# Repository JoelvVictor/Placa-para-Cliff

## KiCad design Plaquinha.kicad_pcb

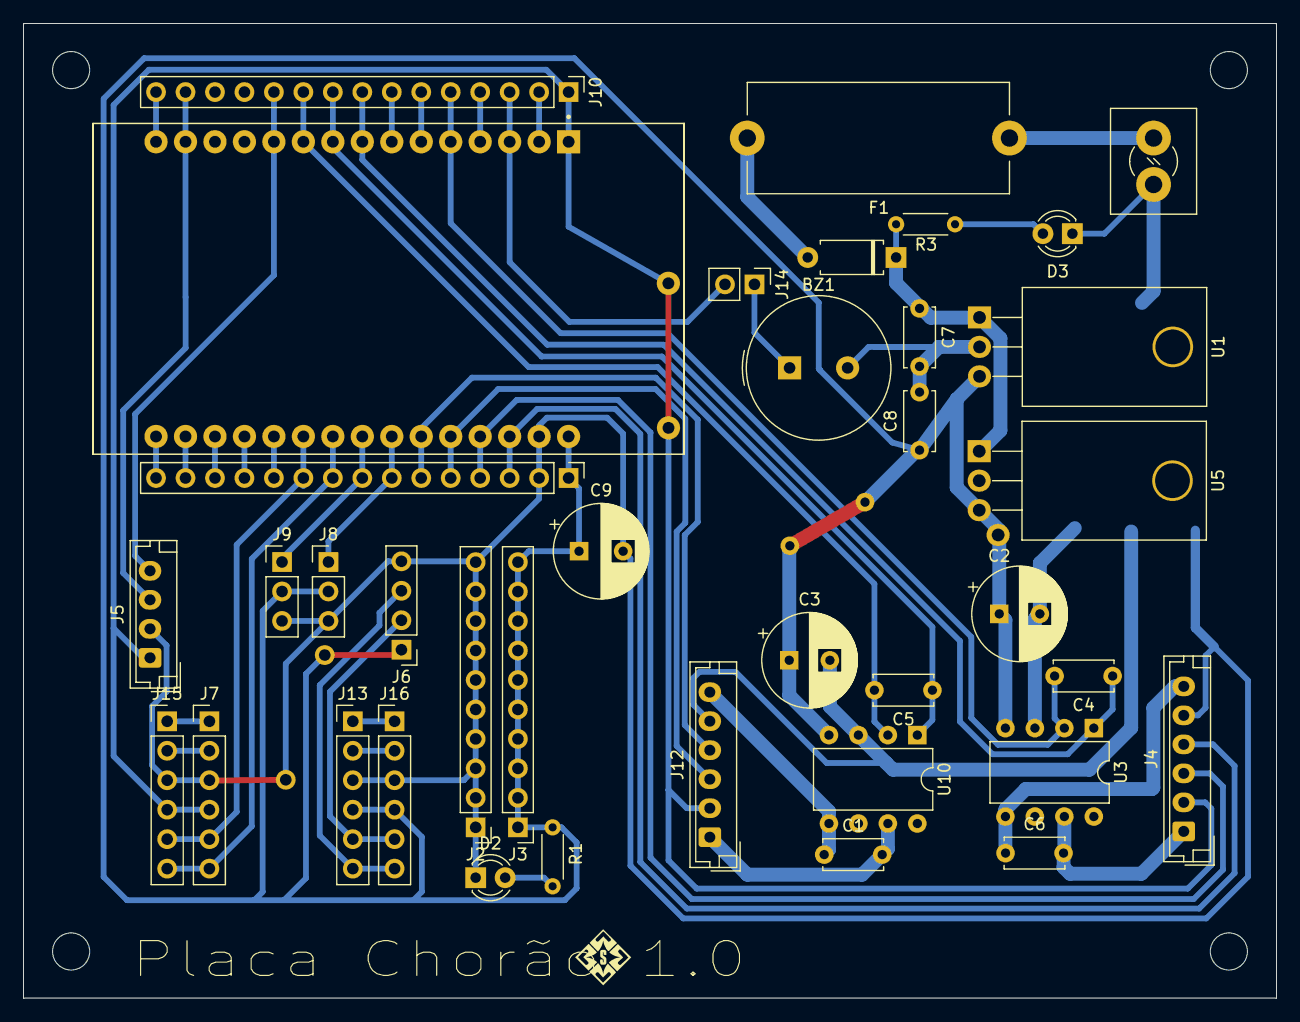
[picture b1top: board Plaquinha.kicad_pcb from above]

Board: 2 copper layers, 108.0 x 84.0 mm, 37 parts (0 on the bottom side), 38 nets.

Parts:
BZ1: Buzzer; Buzzer_TDK_PS1240P02BT_D12.2mm_H6.5mm
C1, C4, C5, C6: C_Small; C_Disc_D5.0mm_W2.5mm_P5.00mm
C2, C3: 100µF; CP_Radial_D8.0mm_P3.50mm
C7: 0.33µF; C_Disc_D5.0mm_W2.5mm_P5.00mm
C8: 0.1µF; C_Disc_D5.0mm_W2.5mm_P5.00mm
C9: 100µF; CP_Radial_D8.0mm_P3.80mm
D1: D; D_A-405_P7.62mm_Horizontal
D2, D3: LED; LED_D3.0mm
F1: 3A; Fuseholder_Cylinder-5x20mm_Stelvio-Kontek_PTF78_Horizontal_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
J1: Screw_Terminal_01x02; TerminalBlock_MetzConnect_360291_1x01_Horizontal_ScrewM3.0_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
J2, J3: Conn_01x10_Socket; PinHeader_1x10_P2.54mm_Vertical
J4, J12: Conn_01x06_Socket; JST_EH_B6B-EH-A_1x06_P2.50mm_Vertical
J5: Conn_01x04_Socket; JST_EH_B4B-EH-A_1x04_P2.50mm_Vertical
J6: Conn_01x04_Socket; PinHeader_1x04_P2.54mm_Vertical
J7, J13, J15, J16: Conn_01x06_Socket; PinHeader_1x06_P2.54mm_Vertical
J8, J9: Conn_01x03_Socket; PinHeader_1x03_P2.54mm_Vertical
J10, J11: Conn_01x15_Socket; PinHeader_1x15_P2.54mm_Vertical
J14: Conn_01x06_Socket; PinHeader_1x02_P2.54mm_Vertical
R1: R_US; R_Axial_DIN0204_L3.6mm_D1.6mm_P5.08mm_Horizontal
R3: R_Small_US; R_Axial_DIN0204_L3.6mm_D1.6mm_P5.08mm_Horizontal
U1, U5: L7805; TO-220-3_Horizontal_TabDown
U3, U10: TA6586; DIP-8_W7.62mm
U9: ESP32-DEVKIT-V1; MODULE_ESP32_DEVKIT_V1

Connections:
3.3V: J4.2, J5.1, J7.4, J10.1, J12.2, J15.4, U9.1 (3V3)
+5V: C2.1, C3.1, C8.1, C9.1, J3.1, J3.2, J3.3, J3.4, J3.5, J3.6, J3.7, J3.8, J3.9, J3.10, J6.1, J8.2, J9.2, J11.1, J13.4, J16.4, R1.1, U1.3 (OUT), U3.4 (VCC), U5.3 (OUT), U9.30 (VIN), U10.4 (VCC)
+12V: F1.1, J1.1
BUZZER: BZ1.1 (+), J10.3, J14.1, J14.2, U9.3 (D15)
D2: J10.4, U9.4 (D2)
D23: J10.15, U9.15 (D23)
D34: J11.12, U9.19 (D34)
D35: J11.11, U9.20 (D35)
ECHO3V: J7.6, J11.9, J15.6, U9.22 (D33)
ECHO5V: J6.3, J13.6, J16.6
EN: J11.15, U9.16 (EN)
GND: BZ1.2 (-), C2.2, C3.2, C7.2, C8.2, C9.2, D2.1 (K), D3.1 (K), J1.2, J2.1, J2.2, J2.3, J2.4, J2.5, J2.6, J2.7, J2.8, J2.9, J2.10, J4.5, J5.2, J6.4, J7.3, J8.3, J9.3, J10.2, J11.2, J12.5, J13.3, J15.3, J16.3, U1.2 (GND), U3.3 (GND), U5.2 (GND), U9.2 (GND), U9.29 (GND__1), U10.3 (GND)
IN1: C5.1, J10.9, U9.9 (D18), U10.1 (BI)
IN2: C5.2, J10.10, U9.10 (D19), U10.2 (FI)
IN3: C4.1, J10.8, U3.1 (BI), U9.8 (D5)
IN4: C4.2, J10.5, U3.2 (FI), U9.5 (D4)
unnamed: D1.2 (A), F1.2
unnamed: C7.1, D1.1 (K), R3.1, U1.1 (IN), U5.1 (IN)
unnamed: D2.2 (A), R1.2
unnamed: D3.2 (A), R3.2
OUTMOT1: C1.1, J12.6, U10.5 (FO)
OUTMOT2: C1.2, J12.1, U10.7 (BO)
OUTMOT3: C6.1, J4.6, U3.5 (FO)
OUTMOT4: C6.2, J4.1, U3.7 (BO)
RX2: J10.6, U9.6 (RX2)
SCL: J5.3, J10.14, U9.14 (D22)
SDA: J5.4, J10.11, U9.11 (D21)
TRIG3V: J7.5, J11.10, J15.5, U9.21 (D32)
TRIG5V: J6.2, J13.5, J16.5
TX2: J10.7, U9.7 (TX2)
VN: J11.13, U9.18 (VN)
VP: J11.14, U9.17 (VP)
encode1 A: J4.4, J11.3, U9.28 (D13)
encode1 B: J4.3, J11.4, U9.27 (D12)
encode2 A: J11.6, J12.4, U9.25 (D27)
encode2 B: J11.5, J12.3, U9.26 (D14)
sinal1: J8.1, J11.7, U9.24 (D26)
sinal2: J9.1, J11.8, U9.23 (D25)

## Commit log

2025-04-23 Criou pasta roubado
2025-04-25 Create temporario
2025-04-25 Create temp
2025-04-26 Subindo projeto Kicad
2025-04-27 Refazendo a cagada
2025-04-28 Conversor lógico atualizado
2025-04-29 PCB e Sketch atualizados
2025-04-30 PCI finalizada e shunt jumper adicionado ao sketch
2025-05-07 Atualizei PCI, tirei jumpers desnecessários e simplifiquei trilhas
2025-05-07 Placa corrigida e pronta para impressão
